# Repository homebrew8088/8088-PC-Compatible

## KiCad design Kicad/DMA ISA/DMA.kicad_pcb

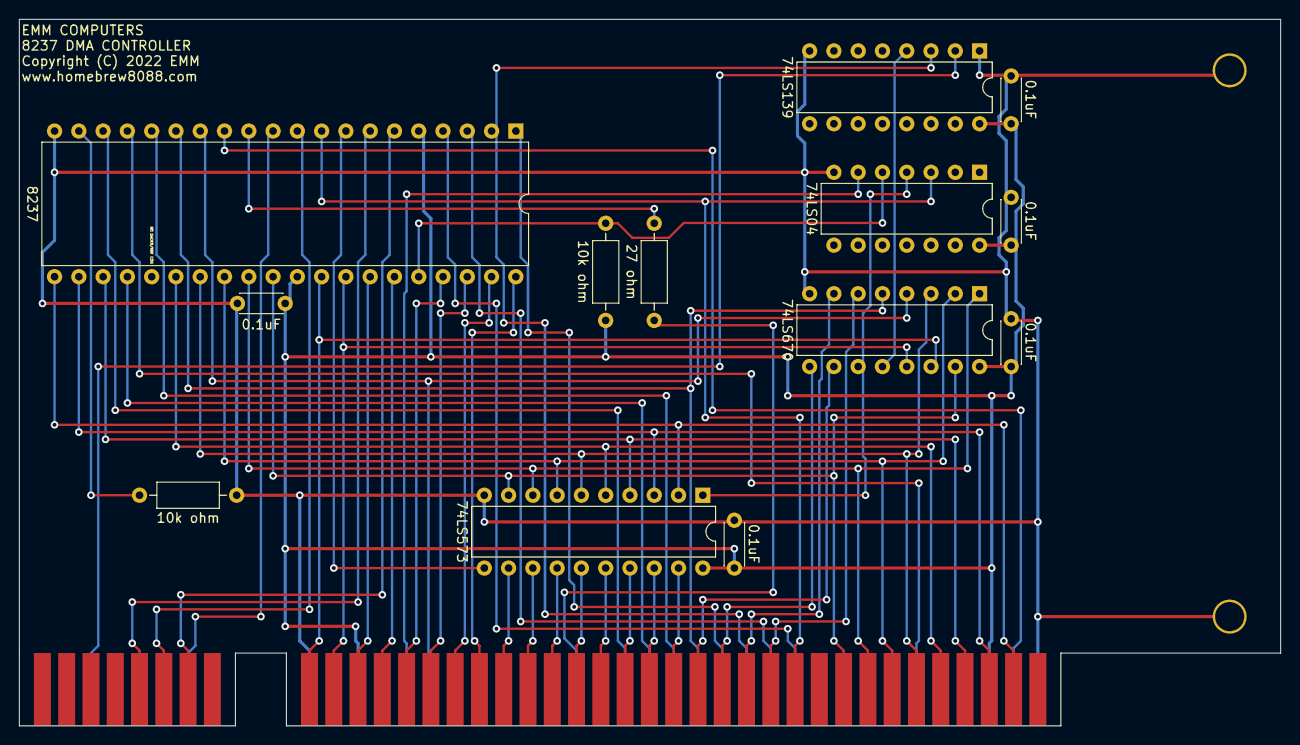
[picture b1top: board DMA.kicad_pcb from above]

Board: 2 copper layers, 132.0 x 73.9 mm, 17 parts (0 on the bottom side), 55 nets.

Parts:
C1, C2, C3, C4, C5: 0.1uF; C_Disc_D4.3mm_W1.9mm_P5.00mm
J1: Conn_02x08_Counter_Clockwise; 16_EDGE_CARD_BUS
J9: Bus_ISA_8bit; BUS_8_BIT
R: L; Large_Via
R1, R2: 10k ohm; R_Axial_DIN0207_L6.3mm_D2.5mm_P10.16mm_Horizontal
R3: 27 ohm; R_Axial_DIN0207_L6.3mm_D2.5mm_P10.16mm_Horizontal
R#2: L; Large_Via
U1: 8237; DIP-40_W15.24mm
U2: 74LS139; DIP-16_W7.62mm
U3: 74LS04; DIP-14_W7.62mm
U4: 74LS670; DIP-16_W7.62mm
U5: 74LS573; DIP-20_W7.62mm

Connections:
/5+: C1.2, C2.2, C3.2, C4.2, C5.2, J9.3, J9.29, R1.2, U1.5, U1.31, U2.16, U3.14, U4.16, U5.20
/760_EN: U2.4, U4.12
/A0: J9.62, U1.32, U4.14
/A1: J9.61, U1.33, U4.13
/A2: J9.60, U1.34
/A3: J9.59, U1.35
/A4: J9.58, U1.37
/A5: J9.57, U1.38
/A6: J9.56, U1.39
/A7: J9.55, U1.40
/A8: J9.54, U5.12
/A9: J9.53, U5.13
/A10: J9.52, U5.14
/A11: J9.51, U5.15
/A12: J9.50, U5.16
/A13: J9.49, U5.17
/A14: J9.48, U5.18
/A15: J9.47, U5.19
/A16: J9.46, U4.10
/A17: J9.45, U4.9
/A18: J9.44, U4.7
/A19: J9.43, U4.6
/ADSTB: U1.8, U5.11
/AEN: J9.42, U1.9, U3.3
/AEN_OE: U3.4, U4.11, U5.1
/CLK88: J9.20, R3.2
/CLK88_1: R3.1, U1.12
/D0: J9.40, U1.30, U4.15, U5.9
/D1: J9.39, U1.29, U4.1, U5.8
/D2: J9.38, U1.28, U4.2, U5.7
/D3: J9.37, U1.27, U4.3, U5.6
/D4: J9.36, U1.26, U5.5
/D5: J9.35, U1.23, U5.4
/D6: J9.34, U1.22, U5.3
/D7: J9.33, U1.21, U5.2
/DACK1: J9.17, U1.24
/DACK2: J9.26, U1.14, U4.4
/DACK3: J9.15, U1.15, U4.5
/DRQ0_: R2.1, U1.19
/DRQ1: J9.18, U1.18
/DRQ2: J9.6, U1.17
/DRQ3: J9.16, U1.16
/EOP: R1.1, U1.36, U3.5
/GND: C1.1, C2.1, C3.1, C4.1, C5.1, J9.1, J9.31, R.1, R2.2, R#2.1, U1.20, U2.1, U2.8, U3.7, U4.8, U5.10
/HOLD: J1.14, U1.10
/HOLDA: J1.13, U1.7
/IORD: J9.14, U1.1
/IOWR: J9.13, U1.2, U2.3
/IO_000X: J1.2, U1.11
/IO_008X: J1.6, U2.2
/MRD: J9.12, U1.3
/MWR: J9.11, U1.4
/READY: J1.15, U1.6
/RESOUT: J9.2, U1.13
/TC: J9.27, U3.6

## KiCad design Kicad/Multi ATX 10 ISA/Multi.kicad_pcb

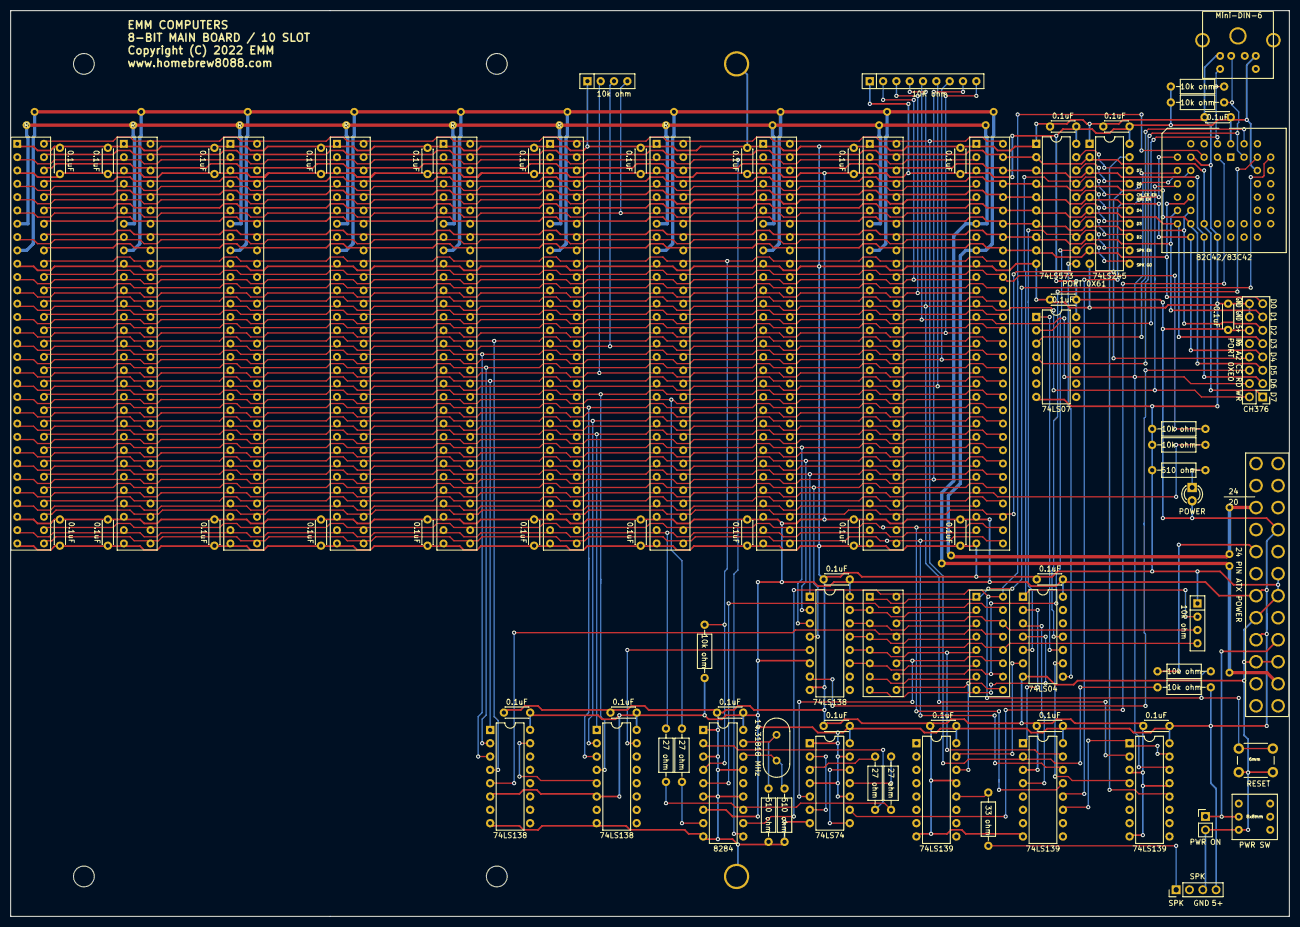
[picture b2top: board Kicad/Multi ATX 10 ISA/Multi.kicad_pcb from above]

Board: 2 copper layers, 243.8 x 172.7 mm, 112 parts (0 on the bottom side), 113 nets.

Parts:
8x8mm1: PWR SW; 6 PIN DTDP
ATXPOWER1: Conn_02x12_Top_Bottom; 24_PIN_ATX_POWER
C1, C1#2, C2, C3, C4, C5, C6, C7, C8, C9, C10, C11, C12, C13, C14, C15, C16, C17, C18, C19, C20, C21, C22, C23, C24, C25, C26, C27, C28, C29, C30, C31, C32, C33: 0.1uF; C_Disc_D4.3mm_W1.9mm_P5.00mm
CH376: PORT 0XE0; PinHeader_2x08_P2.54mm_Vertical
D1: POWER; LED_D3.0mm
J1, J4, J5, J7, J8, J9, J12, J13, J14, J15: Bus_ISA_8bit; 8-bit-ISA
J2: Mini-DIN-6; 6_PIN_DIN
J3: SPK; PinHeader_1x04_P2.54mm_Vertical
J6: PWR ON; PinHeader_1x02_P2.54mm_Vertical
J10, J11: Conn_02x08_Counter_Clockwise; 2x08_PIN_EDGE_CARD
R: L; Large_Via
R1, R2, R4: 510 ohm; R_Axial_DIN0207_L6.3mm_D2.5mm_P10.16mm_Horizontal
R3, R14, R17, R18: 27 ohm; R_Axial_DIN0207_L6.3mm_D2.5mm_P10.16mm_Horizontal
R5, R6, R7, R8, R9, R12, R13: 10k ohm; R_Axial_DIN0207_L6.3mm_D2.5mm_P10.16mm_Horizontal
R112: 33 ohm; R_Axial_DIN0207_L6.3mm_D2.5mm_P10.16mm_Horizontal
R#2, R#3, R#4, R#5, R#6, R#7, R#8, R#9, R#10, R#11, R#12, R#13, R#14, R#15, R#16, R#17, R#18, R#19, R#20, R#21, R#22, R#23, R#24, R#25, R#26: L; Large_Via
RN1, RN3: 10k ohm; R_Array_SIP4
RN2: 10K ohm; R_Array_SIP9
SW1: RESET; SW_PUSH_6mm
U1: 74LS573; DIP-20_W7.62mm
U2: 74LS245; DIP-20_W7.62mm
U3: 82C42/83C42; PLCC-44_THT-Socket
U4: 74LS07; DIP-14_W7.62mm
U5, U7, U8: 74LS138; DIP-16_W7.62mm
U6: 74LS04; DIP-14_W7.62mm
U9: 8284; DIP-18_W7.62mm
U10: 74LS74; DIP-14_W7.62mm
U11, U12, U13: 74LS139; DIP-16_W7.62mm
Y2: 14.31818 MHz; Crystal_HC18-U_Vertical

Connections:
/5+: ATXPOWER1.4, ATXPOWER1.6, ATXPOWER1.21, C1.2, C1#2.2, C2.2, C3.2, C4.2, C5.2, C6.2, C7.2, C8.2, C9.2, C10.2, C11.2, C12.2, C13.2, C14.2, C15.2, C16.2, C17.2, C18.2, C19.2, C20.2, C21.2, C22.2, C23.2, C24.2, C25.2, C26.2, C27.2, C28.2, C29.2, C30.2, C31.2, C32.2, C33.2, CH376.12, D1.2, J1.3, J1.29, J2.4, J3.4, J4.3, J4.29, J5.3, J5.29, J7.3, J7.29, J8.3, J8.29, J9.3, J9.29, J12.3, J12.29, J13.3, J13.29, J14.3, J14.29, J15.3, J15.29, R6.1, R7.1, R8.1, R9.1, RN2.1, U1.20, U2.20, U3.38, U3.44, U4.14, U5.6, U5.16, U6.14, U7.6, U7.16, U8.6, U8.16, U9.7, U9.18, U10.1, U10.4, U10.10, U10.13, U10.14, U11.16, U12.16, U13.16
/5-: J1.5, J4.5, J5.5, J7.5, J8.5, J9.5, J12.5, J13.5, J14.5, J15.5
/12+: ATXPOWER1.10, J1.9, J4.9, J5.9, J7.9, J8.9, J9.9, J12.9, J13.9, J14.9, J15.9, R.1, R#3.1, R#5.1, R#7.1, R#9.1, R#11.1, R#13.1, R#14.1, R#18.1, R#20.1, R#21.1, R#24.1, R#26.1
/12-: ATXPOWER1.14, J1.7, J4.7, J5.7, J7.7, J8.7, J9.7, J12.7, J13.7, J14.7, J15.7, R#2.1, R#4.1, R#6.1, R#8.1, R#10.1, R#12.1, R#15.1, R#16.1, R#17.1, R#19.1, R#22.1, R#23.1, R#25.1
/A0: J1.62, J4.62, J5.62, J7.62, J8.62, J9.62, J12.62, J13.62, J14.62, J15.62, U12.14
/A1: J1.61, J4.61, J5.61, J7.61, J8.61, J9.61, J12.61, J13.61, J14.61, J15.61, U12.13
/A2: CH376.8, J1.60, J4.60, J5.60, J7.60, J8.60, J9.60, J12.60, J13.60, J14.60, J15.60, U3.10
/A3: J1.59, J4.59, J5.59, J7.59, J8.59, J9.59, J12.59, J13.59, J14.59, J15.59
/A4: J1.58, J4.58, J5.58, J7.58, J8.58, J9.58, J12.58, J13.58, J14.58, J15.58, U5.4
/A5: J1.57, J4.57, J5.57, J7.57, J8.57, J9.57, J12.57, J13.57, J14.57, J15.57, U5.1
/A6: J1.56, J4.56, J5.56, J7.56, J8.56, J9.56, J12.56, J13.56, J14.56, J15.56, U5.2
/A7: J1.55, J4.55, J5.55, J7.55, J8.55, J9.55, J12.55, J13.55, J14.55, J15.55, U5.3
/A8: J1.54, J4.54, J5.54, J7.54, J8.54, J9.54, J12.54, J13.54, J14.54, J15.54, U8.1
/A9: J1.53, J4.53, J5.53, J7.53, J8.53, J9.53, J12.53, J13.53, J14.53, J15.53, U8.2
/A10: J1.52, J4.52, J5.52, J7.52, J8.52, J9.52, J12.52, J13.52, J14.52, J15.52, U8.3
/A11: J1.51, J4.51, J5.51, J7.51, J8.51, J9.51, J12.51, J13.51, J14.51, J15.51, U8.4
/A12: J1.50, J4.50, J5.50, J7.50, J8.50, J9.50, J12.50, J13.50, J14.50, J15.50, U7.1
/A13: J1.49, J4.49, J5.49, J7.49, J8.49, J9.49, J12.49, J13.49, J14.49, J15.49, U7.2
/A14: J1.48, J4.48, J5.48, J7.48, J8.48, J9.48, J12.48, J13.48, J14.48, J15.48, U7.3
/A15: J1.47, J4.47, J5.47, J7.47, J8.47, J9.47, J12.47, J13.47, J14.47, J15.47, U7.4
/A16: J1.46, J4.46, J5.46, J7.46, J8.46, J9.46, J12.46, J13.46, J14.46, J15.46
/A17: J1.45, J4.45, J5.45, J7.45, J8.45, J9.45, J12.45, J13.45, J14.45, J15.45
/A18: J1.44, J4.44, J5.44, J7.44, J8.44, J9.44, J12.44, J13.44, J14.44, J15.44
/A19: J1.43, J4.43, J5.43, J7.43, J8.43, J9.43, J12.43, J13.43, J14.43, J15.43
/AEN: J1.42, J4.42, J5.42, J7.42, J8.42, J9.42, J12.42, J13.42, J14.42, J15.42, R12.2
/ALE: J1.28, J4.28, J5.28, J7.28, J8.28, J9.28, J12.28, J13.28, J14.28, J15.28
/CH_CK: J1.32, J4.32, J5.32, J7.32, J8.32, J9.32, J12.32, J13.32, J14.32, J15.32, R7.2, U12.2
/CLK: R18.2, U9.8
/CLK88: J1.20, J4.20, J5.20, J7.20, J8.20, J9.20, J12.20, J13.20, J14.20, J15.20, R18.1
/D0: CH376.15, J1.40, J4.40, J5.40, J7.40, J8.40, J9.40, J12.40, J13.40, J14.40, J15.40, U1.9, U2.9, U3.14
/D1: CH376.13, J1.39, J4.39, J5.39, J7.39, J8.39, J9.39, J12.39, J13.39, J14.39, J15.39, U1.8, U2.8, U3.15
/D2: CH376.11, J1.38, J4.38, J5.38, J7.38, J8.38, J9.38, J12.38, J13.38, J14.38, J15.38, U1.7, U2.7, U3.16
/D3: CH376.9, J1.37, J4.37, J5.37, J7.37, J8.37, J9.37, J12.37, J13.37, J14.37, J15.37, U1.6, U2.6, U3.17
/D4: CH376.7, J1.36, J4.36, J5.36, J7.36, J8.36, J9.36, J12.36, J13.36, J14.36, J15.36, U1.5, U2.5, U3.18
/D5: CH376.5, J1.35, J4.35, J5.35, J7.35, J8.35, J9.35, J12.35, J13.35, J14.35, J15.35, U1.4, U2.4, U3.19
/D6: CH376.3, J1.34, J4.34, J5.34, J7.34, J8.34, J9.34, J12.34, J13.34, J14.34, J15.34, U1.3, U2.3, U3.20
/D7: CH376.1, J1.33, J4.33, J5.33, J7.33, J8.33, J9.33, J12.33, J13.33, J14.33, J15.33, U1.2, U2.2, U3.21
/DACK1: J1.17, J4.17, J5.17, J7.17, J8.17, J9.17, J12.17, J13.17, J14.17, J15.17, RN2.7
/DACK2: J1.26, J4.26, J5.26, J7.26, J8.26, J9.26, J12.26, J13.26, J14.26, J15.26, RN2.8
/DACK3: J1.15, J4.15, J5.15, J7.15, J8.15, J9.15, J12.15, J13.15, J14.15, J15.15, RN2.9
/DRQ0: J10.12, J11.12, RN3.4
/DRQ1: J1.18, J4.18, J5.18, J7.18, J8.18, J9.18, J12.18, J13.18, J14.18, J15.18, RN1.2
/DRQ2: J1.6, J4.6, J5.6, J7.6, J8.6, J9.6, J12.6, J13.6, J14.6, J15.6, RN1.4
/DRQ3: J1.16, J4.16, J5.16, J7.16, J8.16, J9.16, J12.16, J13.16, J14.16, J15.16, RN1.3
/FB1: U10.8, U10.12
/FB2: U10.2, U10.6
/GND: 8x8mm1.3, ATXPOWER1.3, ATXPOWER1.5, ATXPOWER1.15, ATXPOWER1.18, ATXPOWER1.19, C1.1, C1#2.1, C2.1, C3.1, C4.1, C5.1, C6.1, C7.1, C8.1, C9.1, C10.1, C11.1, C12.1, C13.1, C14.1, C15.1, C16.1, C17.1, C18.1, C19.1, C20.1, C21.1, C22.1, C23.1, C24.1, C25.1, C26.1, C27.1, C28.1, C29.1, C30.1, C31.1, C32.1, C33.1, CH376.14, CH376.16, J1.1, J1.10, J1.31, J2.3, J3.3, J4.1, J4.10, J4.31, J5.1, J5.10, J5.31, J6.2, J7.1, J7.10, J7.31, J8.1, J8.10, J8.31, J9.1, J9.10, J9.31, J12.1, J12.10, J12.31, J13.1, J13.10, J13.31, J14.1, J14.10, J14.31, J15.1, J15.10, J15.31, R1.2, R2.2, R4.2, R12.1, R13.1, RN1.1, RN3.1, SW1.2, U1.1, U1.10, U2.1, U2.10, U3.8, U3.22, U4.7, U5.8, U6.7, U7.8, U8.8, U9.1, U9.3, U9.6, U9.9, U9.13, U9.15, U10.7, U11.8, U11.13, U12.3, U12.8, U13.3, U13.8, U13.13
/HF_OSC: U3.3, U10.9
/HF_PCLK: J10.11, J11.11, U10.5
/HOLD: J10.14, J11.14, RN3.3
/HOLDA: J10.13, J11.13, U7.5
/IORD: CH376.4, J1.14, J4.14, J5.14, J7.14, J8.14, J9.14, J12.14, J13.14, J14.14, J15.14, RN2.5, U3.9, U13.14
/IOWR: CH376.2, J1.13, J4.13, J5.13, J7.13, J8.13, J9.13, J12.13, J13.13, J14.13, J15.13, RN2.4, U3.11, U13.2
/IO_00EX: CH376.6, U5.7
/IO_000X: J10.2, J11.2, U5.15
/IO_00XX: U5.5, U8.15
/IO_0XXX: U7.15, U8.5
/IO_002X: J10.3, J11.3, U5.14
/IO_004X: J10.4, J11.4, U5.13
/IO_006X: J10.5, J11.5, U5.12, U12.15
/IO_008X: J10.6, J11.6, U5.11
/IO_0060: U3.7, U12.12
/IO_0061: U12.11, U13.1, U13.15
/IRQ1: J10.1, J11.1, U3.39
/IRQ2: J1.4, J4.4, J5.4, J7.4, J8.4, J9.4, J12.4, J13.4, J14.4, J15.4
/IRQ3: J1.25, J4.25, J5.25, J7.25, J8.25, J9.25, J12.25, J13.25, J14.25, J15.25
/IRQ4: J1.24, J4.24, J5.24, J7.24, J8.24, J9.24, J12.24, J13.24, J14.24, J15.24
/IRQ5: J1.23, J4.23, J5.23, J7.23, J8.23, J9.23, J12.23, J13.23, J14.23, J15.23
/IRQ6: J1.22, J4.22, J5.22, J7.22, J8.22, J9.22, J12.22, J13.22, J14.22, J15.22
/IRQ7: J1.21, J4.21, J5.21, J7.21, J8.21, J9.21, J12.21, J13.21, J14.21, J15.21
/KBD_CLK: U3.41, U6.11
/KBD_CLK_INVERTED: U4.1, U6.10
/KBD_DATA: U3.42, U4.3
/LED_GND: D1.1, R1.1
/MRD: J1.12, J4.12, J5.12, J7.12, J8.12, J9.12, J12.12, J13.12, J14.12, J15.12, RN2.3
/MWR: J1.11, J4.11, J5.11, J7.11, J8.11, J9.11, J12.11, J13.11, J14.11, J15.11, RN2.2
/NC: J1.8, J4.8, J5.8, J7.8, J8.8, J9.8, J12.8, J13.8, J14.8, J15.8
/NC_1: J10.7, J11.7
/NMI: J10.8, J11.8, U6.4
/NMI_EN: RN3.2, U1.17, U2.16, U6.1
/NMI_EN_139: U6.2, U12.1
/NMI_INPUT: U6.3, U12.4
/OSC: R3.2, R14.2, U9.12
/OSC88: J1.30, J4.30, J5.30, J7.30, J8.30, J9.30, J12.30, J13.30, J14.30, J15.30, R14.1
/OSC88HF: R3.1, U10.11
/PCLK: R17.2, U9.2
/PCLK88: R17.1, U10.3
/PORT_0X61_CS: U1.11, U6.8
/PORT_0X61_EN: U6.9, U13.4
/PORT_61_2: U1.14, U2.13
/PORT_61_3: U1.15, U2.14
/PORT_61_4: U1.16, U2.15
/PORT_61_6: U1.18, U2.17
/PORT_61_7: U1.19, U2.18
/PORT_61_RD: U2.19, U13.12
/POWER_GOOD: ATXPOWER1.8, R5.1
/POWER_ON: 8x8mm1.2, ATXPOWER1.16, J6.1
/RDY1: J1.41, J4.41, J5.41, J7.41, J8.41, J9.41, J12.41, J13.41, J14.41, J15.41, R6.2, U9.4
/READY: J10.15, J11.15, U9.5
/REFRQ: J1.19, J4.19, J5.19, J7.19, J8.19, J9.19, J12.19, J13.19, J14.19, J15.19, RN2.6
/RESET: J10.16, J11.16, R5.2, SW1.1, U3.5, U9.11
/RESOUT: J1.2, J4.2, J5.2, J7.2, J8.2, J9.2, J12.2, J13.2, J14.2, J15.2, U9.10
/SPK_EN: U1.13, U2.12, U6.5
/SPK_EN_: U6.6, U11.15
/SPK_GO: J10.10, J11.10, U1.12, U2.11
/SPK_OUT: J10.9, J11.9, U11.14
/SPK_PIN: R112.2, U11.12
/SPK_PIN_O: J3.1, R112.1
/T0: J2.5, R8.2, U3.2, U4.2
/T1: J2.1, R9.2, U3.43, U4.4
/TC: J1.27, J4.27, J5.27, J7.27, J8.27, J9.27, J12.27, J13.27, J14.27, J15.27, R13.2
/X1_8284: R4.1, U9.17, Y2.2
/X2_8284: R2.1, U9.16, Y2.1

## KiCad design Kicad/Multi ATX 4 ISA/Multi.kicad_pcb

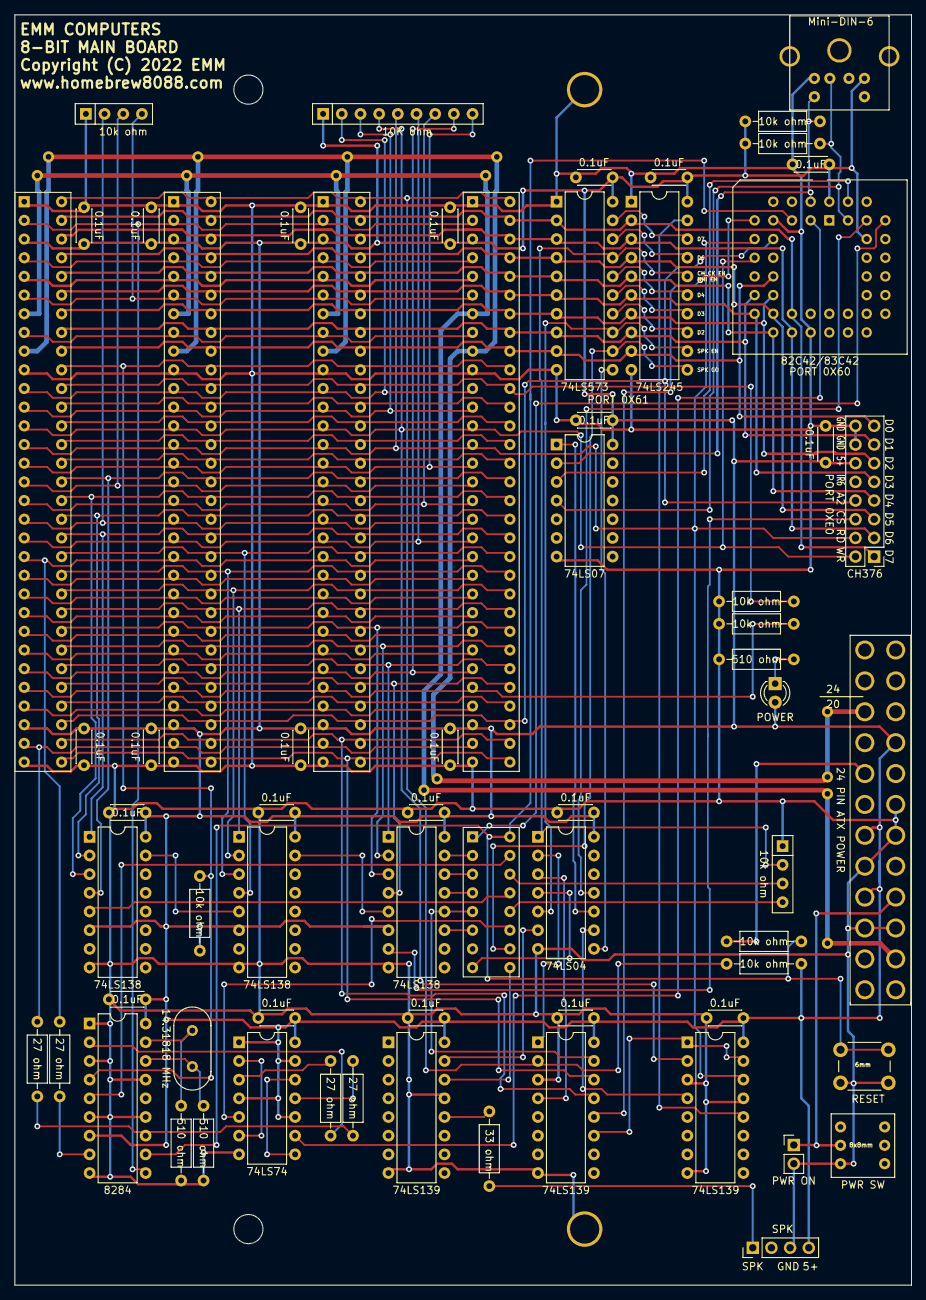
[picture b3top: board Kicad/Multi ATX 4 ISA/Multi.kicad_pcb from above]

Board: 2 copper layers, 121.9 x 172.7 mm, 81 parts (0 on the bottom side), 112 nets.

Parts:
8x8mm1: PWR SW; 6 PIN DTDP
ATXPOWER1: Conn_02x12_Top_Bottom; 24_PIN_ATX_POWER
C1, C1#2, C2, C3, C4, C5, C6, C7, C8, C9, C10, C11, C12, C13, C22, C23, C24, C25, C26, C27, C28, C29: 0.1uF; C_Disc_D4.3mm_W1.9mm_P5.00mm
CH376: PORT 0XE0; PinHeader_2x08_P2.54mm_Vertical
D1: POWER; LED_D3.0mm
J1, J7, J8, J9: Bus_ISA_8bit; 8-bit-ISA
J2: Mini-DIN-6; 6_PIN_DIN
J3: SPK; PinHeader_1x04_P2.54mm_Vertical
J6: PWR ON; PinHeader_1x02_P2.54mm_Vertical
J10: Conn_02x08_Counter_Clockwise; 2x08_PIN_EDGE_CARD
R: L; Large_Via
R1, R2, R4: 510 ohm; R_Axial_DIN0207_L6.3mm_D2.5mm_P10.16mm_Horizontal
R3, R14, R17, R18: 27 ohm; R_Axial_DIN0207_L6.3mm_D2.5mm_P10.16mm_Horizontal
R5, R6, R7, R8, R9, R12, R13: 10k ohm; R_Axial_DIN0207_L6.3mm_D2.5mm_P10.16mm_Horizontal
R#2, R#3, R#4, R#5, R#6, R#7, R#8, R#9, R#10, R#11, R#12, R#13, R#14: L; Large_Via
RN1, RN3: 10k ohm; R_Array_SIP4
RN2: 10K ohm; R_Array_SIP9
SW1: RESET; SW_PUSH_6mm
U1, U17, U117: 74LS139; DIP-16_W7.62mm
U2: 74LS245; DIP-20_W7.62mm
U3: 33 ohm; R_Axial_DIN0207_L6.3mm_D2.5mm_P10.16mm_Horizontal
U9, U12, U13: 74LS138; DIP-16_W7.62mm
U11: 8284; DIP-18_W7.62mm
U14: 74LS74; DIP-14_W7.62mm
U15: 74LS573; DIP-20_W7.62mm
U16: 74LS04; DIP-14_W7.62mm
U19: 82C42/83C42; PLCC-44_THT-Socket
U20: 74LS07; DIP-14_W7.62mm
Y2: 14.31818 MHz; Crystal_HC18-U_Vertical

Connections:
/5+: ATXPOWER1.4, ATXPOWER1.6, ATXPOWER1.21, C1.2, C1#2.2, C2.2, C3.2, C4.2, C5.2, C6.2, C7.2, C8.2, C9.2, C10.2, C11.2, C12.2, C13.2, C22.2, C23.2, C24.2, C25.2, C26.2, C27.2, C28.2, C29.2, CH376.12, D1.2, J1.3, J1.29, J2.4, J3.4, J7.3, J7.29, J8.3, J8.29, J9.3, J9.29, R6.1, R7.1, R8.1, R9.1, RN2.1, U1.16, U2.20, U9.6, U9.16, U11.7, U11.18, U12.6, U12.16, U13.6, U13.16, U14.1, U14.4, U14.10, U14.13, U14.14, U15.20, U16.14, U17.16, U19.38, U19.44, U20.14, U117.16
/5-: J1.5, J7.5, J8.5, J9.5
/12+: ATXPOWER1.10, J1.9, J7.9, J8.9, J9.9, R.1, R#2.1, R#6.1, R#8.1, R#9.1, R#12.1, R#14.1
/12-: ATXPOWER1.14, J1.7, J7.7, J8.7, J9.7, R#3.1, R#4.1, R#5.1, R#7.1, R#10.1, R#11.1, R#13.1
/A0: J1.62, J7.62, J8.62, J9.62, U17.14
/A1: J1.61, J7.61, J8.61, J9.61, U17.13
/A2: CH376.8, J1.60, J7.60, J8.60, J9.60, U19.10
/A3: J1.59, J7.59, J8.59, J9.59
/A4: J1.58, J7.58, J8.58, J9.58, U13.4
/A5: J1.57, J7.57, J8.57, J9.57, U13.1
/A6: J1.56, J7.56, J8.56, J9.56, U13.2
/A7: J1.55, J7.55, J8.55, J9.55, U13.3
/A8: J1.54, J7.54, J8.54, J9.54, U12.1
/A9: J1.53, J7.53, J8.53, J9.53, U12.2
/A10: J1.52, J7.52, J8.52, J9.52, U12.3
/A11: J1.51, J7.51, J8.51, J9.51, U12.4
/A12: J1.50, J7.50, J8.50, J9.50, U9.1
/A13: J1.49, J7.49, J8.49, J9.49, U9.2
/A14: J1.48, J7.48, J8.48, J9.48, U9.3
/A15: J1.47, J7.47, J8.47, J9.47, U9.4
/A16: J1.46, J7.46, J8.46, J9.46
/A17: J1.45, J7.45, J8.45, J9.45
/A18: J1.44, J7.44, J8.44, J9.44
/A19: J1.43, J7.43, J8.43, J9.43
/AEN: J1.42, J7.42, J8.42, J9.42, R12.2
/ALE: J1.28, J7.28, J8.28, J9.28
/CH_CK: J1.32, J7.32, J8.32, J9.32, R7.2, U17.2
/CLK: R18.2, U11.8
/CLK88: J1.20, J7.20, J8.20, J9.20, R18.1
/D0: CH376.15, J1.40, J7.40, J8.40, J9.40, U2.9, U15.9, U19.14
/D1: CH376.13, J1.39, J7.39, J8.39, J9.39, U2.8, U15.8, U19.15
/D2: CH376.11, J1.38, J7.38, J8.38, J9.38, U2.7, U15.7, U19.16
/D3: CH376.9, J1.37, J7.37, J8.37, J9.37, U2.6, U15.6, U19.17
/D4: CH376.7, J1.36, J7.36, J8.36, J9.36, U2.5, U15.5, U19.18
/D5: CH376.5, J1.35, J7.35, J8.35, J9.35, U2.4, U15.4, U19.19
/D6: CH376.3, J1.34, J7.34, J8.34, J9.34, U2.3, U15.3, U19.20
/D7: CH376.1, J1.33, J7.33, J8.33, J9.33, U2.2, U15.2, U19.21
/DACK1: J1.17, J7.17, J8.17, J9.17, RN2.7
/DACK2: J1.26, J7.26, J8.26, J9.26, RN2.8
/DACK3: J1.15, J7.15, J8.15, J9.15, RN2.9
/DRQ0: J10.12, RN3.4
/DRQ1: J1.18, J7.18, J8.18, J9.18, RN1.2
/DRQ2: J1.6, J7.6, J8.6, J9.6, RN1.4
/DRQ3: J1.16, J7.16, J8.16, J9.16, RN1.3
/FB1: U14.8, U14.12
/FB2: U14.2, U14.6
/GND: 8x8mm1.3, ATXPOWER1.3, ATXPOWER1.5, ATXPOWER1.15, ATXPOWER1.18, ATXPOWER1.19, C1.1, C1#2.1, C2.1, C3.1, C4.1, C5.1, C6.1, C7.1, C8.1, C9.1, C10.1, C11.1, C12.1, C13.1, C22.1, C23.1, C24.1, C25.1, C26.1, C27.1, C28.1, C29.1, CH376.14, CH376.16, J1.1, J1.10, J1.31, J2.3, J3.3, J6.2, J7.1, J7.10, J7.31, J8.1, J8.10, J8.31, J9.1, J9.10, J9.31, R1.2, R2.2, R4.2, R12.1, R13.1, RN1.1, RN3.1, SW1.2, U1.3, U1.8, U1.13, U2.1, U2.10, U9.8, U11.1, U11.3, U11.6, U11.9, U11.13, U11.15, U12.8, U13.8, U14.7, U15.1, U15.10, U16.7, U17.3, U17.8, U19.8, U19.22, U20.7, U117.8, U117.13
/HF_OSC: U14.9, U19.3
/HF_PCLK: J10.11, U14.5
/HOLD: J10.14, RN3.3
/HOLDA: J10.13, U9.5
/IORD: CH376.4, J1.14, J7.14, J8.14, J9.14, RN2.5, U1.14, U19.9
/IOWR: CH376.2, J1.13, J7.13, J8.13, J9.13, RN2.4, U1.2, U19.11
/IO_00EX: CH376.6, U13.7
/IO_000X: J10.2, U13.15
/IO_00XX: U12.15, U13.5
/IO_0XXX: U9.15, U12.5
/IO_002X: J10.3, U13.14
/IO_004X: J10.4, U13.13
/IO_006X: J10.5, U13.12, U17.15
/IO_008X: J10.6, U13.11
/IO_0060: U17.12, U19.7
/IO_0061: U1.1, U1.15, U17.11
/IRQ1: J10.1, U19.39
/IRQ2: J1.4, J7.4, J8.4, J9.4
/IRQ3: J1.25, J7.25, J8.25, J9.25
/IRQ4: J1.24, J7.24, J8.24, J9.24
/IRQ5: J1.23, J7.23, J8.23, J9.23
/IRQ6: J1.22, J7.22, J8.22, J9.22
/IRQ7: J1.21, J7.21, J8.21, J9.21
/KBD_CLK: U16.11, U19.41
/KBD_CLK_INVERTED: U16.10, U20.1
/KBD_DATA: U19.42, U20.3
/LED_GND: D1.1, R1.1
/MRD: J1.12, J7.12, J8.12, J9.12, RN2.3
/MWR: J1.11, J7.11, J8.11, J9.11, RN2.2
/NC: J1.8, J7.8, J8.8, J9.8
/NMI: J10.8, U16.4
/NMI_EN: RN3.2, U2.16, U15.17, U16.1
/NMI_EN_139: U16.2, U17.1
/NMI_INPUT: U16.3, U17.4
/OSC: R3.2, R14.2, U11.12
/OSC88: J1.30, J7.30, J8.30, J9.30, R14.1
/OSC88HF: R3.1, U14.11
/PCLK: R17.2, U11.2
/PCLK88: R17.1, U14.3
/PORT_0X61_CS: U15.11, U16.8
/PORT_0X61_EN: U1.4, U16.9
/PORT_61_2: U2.13, U15.14
/PORT_61_3: U2.14, U15.15
/PORT_61_4: U2.15, U15.16
/PORT_61_6: U2.17, U15.18
/PORT_61_7: U2.18, U15.19
/PORT_61_RD: U1.12, U2.19
/POWER_GOOD: ATXPOWER1.8, R5.1
/POWER_ON: 8x8mm1.2, ATXPOWER1.16, J6.1
/RDY1: J1.41, J7.41, J8.41, J9.41, R6.2, U11.4
/READY: J10.15, U11.5
/REFRQ: J1.19, J7.19, J8.19, J9.19, RN2.6
/RESET: J10.16, R5.2, SW1.1, U11.11, U19.5
/RESOUT: J1.2, J7.2, J8.2, J9.2, U11.10
/SPK_EN: U2.12, U15.13, U16.5
/SPK_EN_: U16.6, U117.15
/SPK_GO: J10.10, U2.11, U15.12
/SPK_OUT: J10.9, U117.14
/SPK_PIN: U3.2, U117.12
/SPK_PIN_O: J3.1, U3.1
/T0: J2.5, R8.2, U19.2, U20.2
/T1: J2.1, R9.2, U19.43, U20.4
/TC: J1.27, J7.27, J8.27, J9.27, R13.2
/X1_8284: R4.1, U11.17, Y2.2
/X2_8284: R2.1, U11.16, Y2.1

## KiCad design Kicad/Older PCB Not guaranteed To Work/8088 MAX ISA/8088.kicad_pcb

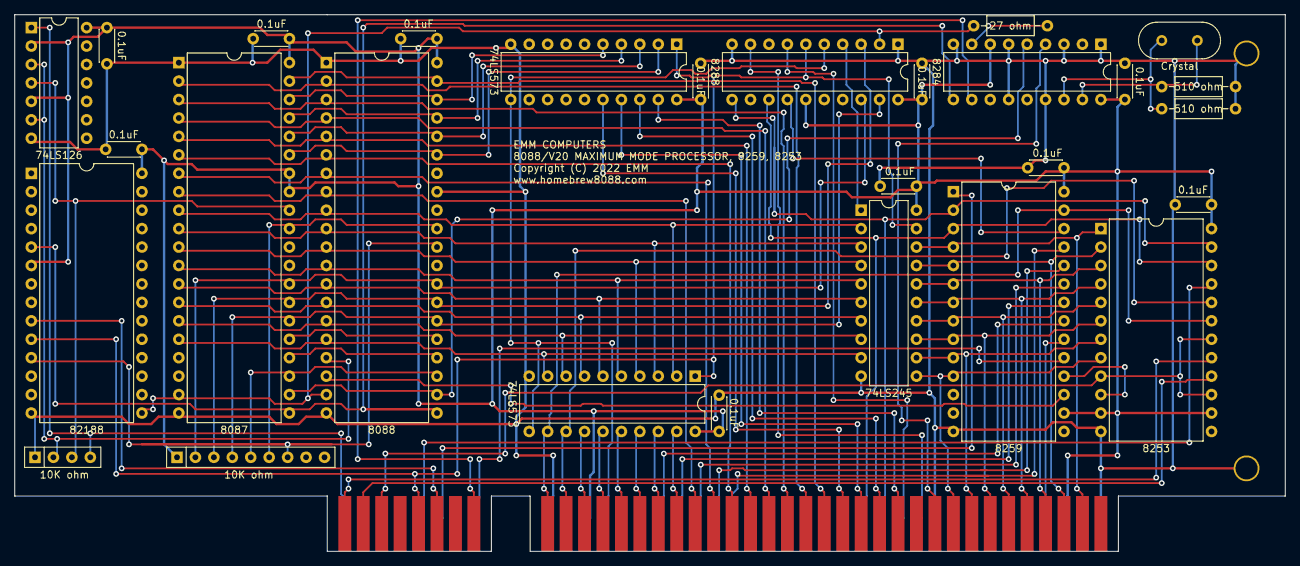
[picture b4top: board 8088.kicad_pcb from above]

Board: 2 copper layers, 175.0 x 73.9 mm, 32 parts (0 on the bottom side), 84 nets.

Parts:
C1, C2, C3, C4, C5, C6, C7, C8, C9, C10, C11: 0.1uF; C_Disc_D4.3mm_W1.9mm_P5.00mm
J1: Conn_02x08_Counter_Clockwise; 16_EDGE_CARD_BUS
J9: Bus_ISA_8bit; BUS_8_BIT
R: L; Large_Via
R1: 27 ohm; R_Axial_DIN0207_L6.3mm_D2.5mm_P10.16mm_Horizontal
R2, R3: 510 ohm; R_Axial_DIN0207_L6.3mm_D2.5mm_P10.16mm_Horizontal
R#2: L; Large_Via
RN1: 10K ohm; R_Array_SIP9
RN2: 10K ohm; R_Array_SIP4
U1: 8088; DIP-40_W15.24mm
U2, U3: 74LS573; DIP-20_W7.62mm
U4: 74LS245; DIP-20_W7.62mm
U5: 82188; DIP-28_W15.24mm
U6: 8284; DIP-18_W7.62mm
U7: 8259; DIP-28_W15.24mm
U8: 8253; DIP-24_W15.24mm
U9: 8087; DIP-40_W15.24mm
U10: 8288; DIP-20_W7.62mm
U11: 74LS126; DIP-14_W7.62mm
Y1: Crystal; Crystal_HC18-U_Vertical

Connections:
/5+: C1.2, C2.2, C3.2, C4.2, C5.2, C6.2, C7.2, C8.2, C9.2, C10.2, C11.2, J9.3, J9.29, RN1.1, U1.40, U2.20, U3.20, U4.20, U5.6, U5.28, U6.7, U6.18, U7.16, U7.28, U8.11, U8.14, U8.24, U9.33, U9.34, U9.40, U10.15, U10.20, U11.2, U11.5, U11.14
/8087_INT: RN2.3, U9.32, U11.4
/8088_NMI: RN2.2, U1.17, U11.3, U11.6
/A0: J9.62, U3.12, U7.27, U8.19
/A1: J9.61, U3.13, U8.20
/A2: J9.60, U3.14
/A3: J9.59, U3.15
/A4: J9.58, U3.16
/A5: J9.57, U3.17
/A6: J9.56, U3.18
/A7: J9.55, U3.19
/A8: J9.54, U1.8, U9.8
/A9: J9.53, U1.7, U9.7
/A10: J9.52, U1.6, U9.6
/A11: J9.51, U1.5, U9.5
/A12: J9.50, U1.4, U9.4
/A13: J9.49, U1.3, U9.3
/A14: J9.48, U1.2, U9.2
/A15: J9.47, U1.39, U9.39
/A16: J9.46, U2.16
/A16_: U1.38, U2.5, U9.38
/A17: J9.45, U2.17
/A17_: U1.37, U2.4, U9.37
/A18: J9.44, U2.18
/A18_: U1.36, U2.3, U9.36
/A19: J9.43, U2.19
/A19_: U1.35, U2.2, U9.35
/AD0: U1.16, U3.9, U4.9, U9.16
/AD1: U1.15, U3.8, U4.8, U9.15
/AD2: U1.14, U3.7, U4.7, U9.14
/AD3: U1.13, U3.6, U4.6, U9.13
/AD4: U1.12, U3.5, U4.5, U9.12
/AD5: U1.11, U3.4, U4.4, U9.11
/AD6: U1.10, U3.3, U4.3, U9.10
/AD7: U1.9, U3.2, U4.2, U9.9
/ALE: J9.28, U2.11, U3.11, U10.5
/CLK1: R1.2, U6.8
/CLK_88: R1.1, U1.19, U5.15, U9.19, U10.2
/D0: J9.40, U4.11, U7.11, U8.8
/D1: J9.39, U4.12, U7.10, U8.7
/D2: J9.38, U4.13, U7.9, U8.6
/D3: J9.37, U4.14, U7.8, U8.5
/D4: J9.36, U4.15, U7.7, U8.4
/D5: J9.35, U4.16, U7.6, U8.3
/D6: J9.34, U4.17, U7.5, U8.2
/D7: J9.33, U4.18, U7.4, U8.1
/DTR: U4.1, U10.4
/GND: C1.1, C2.1, C3.1, C4.1, C5.1, C6.1, C7.1, C8.1, C9.1, C10.1, C11.1, J9.1, J9.10, J9.31, R.1, R2.2, R3.2, R#2.1, RN2.1, U1.1, U1.20, U1.33, U2.10, U3.10, U4.10, U5.14, U6.1, U6.3, U6.6, U6.9, U6.13, U6.15, U7.14, U8.12, U9.1, U9.20, U10.1, U10.10, U11.7
/HF_PCLK: J1.11, U8.9, U8.15, U8.18
/HOLD: J1.14, U5.9
/HOLDA: J1.13, U2.1, U3.1, U4.19, U5.10, U10.6
/INTA: U7.26, U10.14
/INTR: U1.18, U7.17
/IORD: J9.14, U7.3, U8.22, U10.13
/IOWR: J9.13, U7.2, U8.23, U10.11
/IO_002X: J1.3, U7.1
/IO_004X: J1.4, U8.21
/IRQ0: U7.18, U8.10
/IRQ1: J1.1, U7.19
/IRQ2: J9.4, U7.20
/IRQ3: J9.25, U7.21
/IRQ4: J9.24, U7.22
/IRQ5: J9.23, U7.23
/IRQ6: J9.22, U7.24
/IRQ7: J9.21, U7.25
/MRD: J9.12, U10.7
/MWR: J9.11, U10.9
/NMI: J1.8, RN2.4, U11.1
/QS0: U1.25, U9.25
/QS1: U1.24, U9.24
/RDY1: J9.41, U6.4
/READY1: U1.22, U6.5, U9.22
/RESET: J1.16, U6.11
/RESET1: U1.21, U5.5, U6.10, U9.21
/RQ_8087: RN1.6, U1.31, U9.31
/RQ_82188: RN1.7, U1.30, U5.11
/S0: RN1.4, U1.26, U9.26, U10.19
/S1: RN1.3, U1.27, U9.27, U10.3
/S2: RN1.2, U1.28, U9.28, U10.18
/SPK_GO: J1.10, U8.16
/SPK_OUT: J1.9, U8.17
/TEST: RN1.5, U1.23, U9.23
/X1: R2.1, U6.17, Y1.2
/X2: R3.1, U6.16, Y1.1

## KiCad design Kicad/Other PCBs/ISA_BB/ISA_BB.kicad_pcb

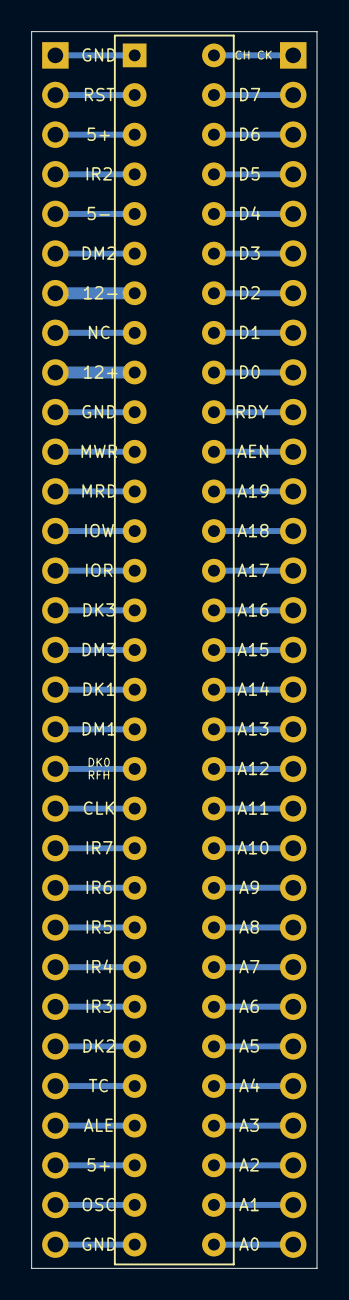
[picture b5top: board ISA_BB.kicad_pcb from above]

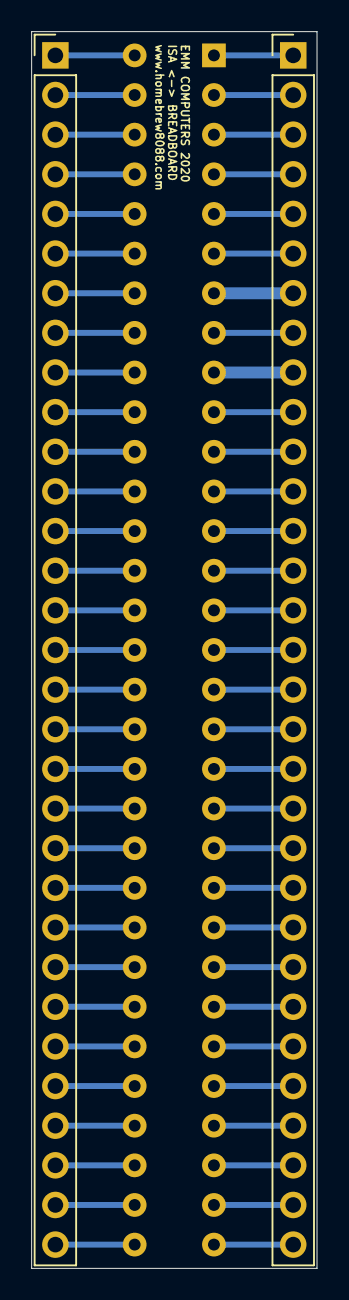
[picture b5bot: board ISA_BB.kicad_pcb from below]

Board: 2 copper layers, 18.3 x 79.2 mm, 3 parts (2 on the bottom side), 62 nets.

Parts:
J1, J3: Conn_01x31; PinHeader_1x31_P2.54mm_Vertical
J2: Bus_ISA_8bit; 8-bit-ISA

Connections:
unnamed: J1.1, J2.1
unnamed: J1.2, J2.2
unnamed: J1.3, J2.3
unnamed: J1.4, J2.4
unnamed: J1.5, J2.5
unnamed: J1.6, J2.6
unnamed: J1.7, J2.7
unnamed: J1.8, J2.8
unnamed: J1.9, J2.9
unnamed: J1.10, J2.10
unnamed: J1.11, J2.11
unnamed: J1.12, J2.12
unnamed: J1.13, J2.13
unnamed: J1.14, J2.14
unnamed: J1.15, J2.15
unnamed: J1.16, J2.16
unnamed: J1.17, J2.17
unnamed: J1.18, J2.18
unnamed: J1.19, J2.19
unnamed: J1.20, J2.20
unnamed: J1.21, J2.21
unnamed: J1.22, J2.22
unnamed: J1.23, J2.23
unnamed: J1.24, J2.24
unnamed: J1.25, J2.25
unnamed: J1.26, J2.26
unnamed: J1.27, J2.27
unnamed: J1.28, J2.28
unnamed: J1.29, J2.29
unnamed: J1.30, J2.30
unnamed: J1.31, J2.31
unnamed: J2.32, J3.1
unnamed: J2.33, J3.2
unnamed: J2.34, J3.3
unnamed: J2.35, J3.4
unnamed: J2.36, J3.5
unnamed: J2.37, J3.6
unnamed: J2.38, J3.7
unnamed: J2.39, J3.8
unnamed: J2.40, J3.9
unnamed: J2.41, J3.10
unnamed: J2.42, J3.11
unnamed: J2.43, J3.12
unnamed: J2.44, J3.13
unnamed: J2.45, J3.14
unnamed: J2.46, J3.15
unnamed: J2.47, J3.16
unnamed: J2.48, J3.17
unnamed: J2.49, J3.18
unnamed: J2.50, J3.19
unnamed: J2.51, J3.20
unnamed: J2.52, J3.21
unnamed: J2.53, J3.22
unnamed: J2.54, J3.23
unnamed: J2.55, J3.24
unnamed: J2.56, J3.25
unnamed: J2.57, J3.26
unnamed: J2.58, J3.27
unnamed: J2.59, J3.28
unnamed: J2.60, J3.29
unnamed: J2.61, J3.30
unnamed: J2.62, J3.31

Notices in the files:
Kicad/DMA ISA/DMA.kicad_pcb:
Copyright (C) 2022 EMM
